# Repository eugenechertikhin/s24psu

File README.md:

This is restore schematic from Studio24 psu for ut88 / rk86

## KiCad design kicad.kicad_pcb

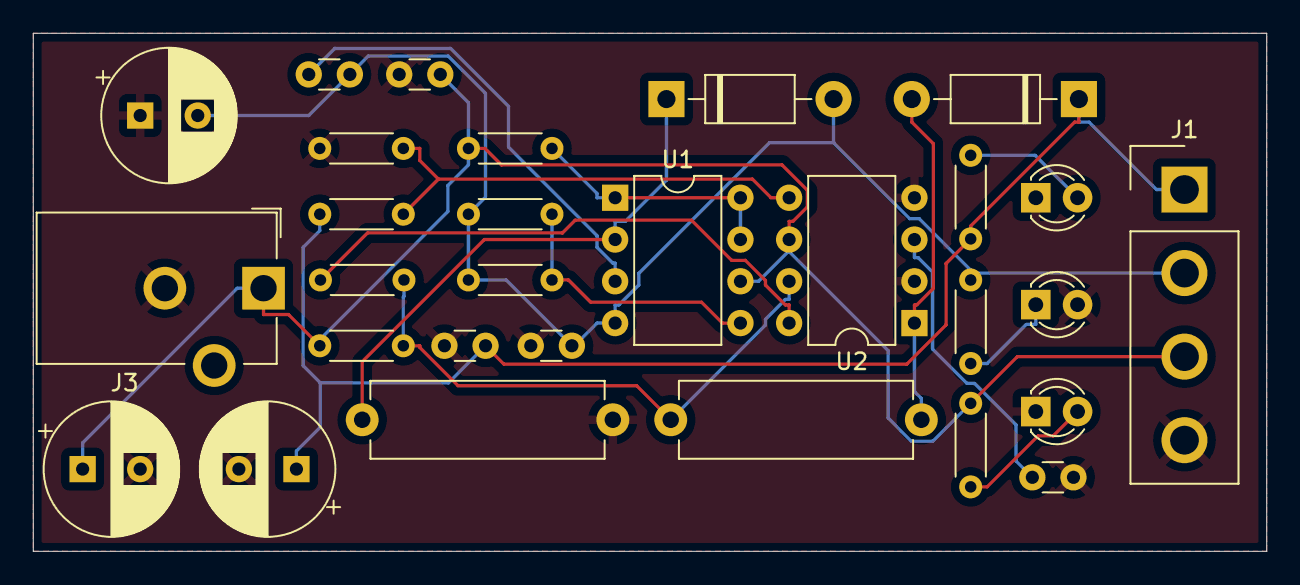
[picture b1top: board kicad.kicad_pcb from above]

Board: 2 copper layers, 75.0 x 31.5 mm, 29 parts (0 on the bottom side), 16 nets.

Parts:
C1, C5, C8: 1000uF 9V; CP_Radial_D8.0mm_P3.50mm
C2, C6: 400pF; C_Disc_D3.0mm_W1.6mm_P2.50mm
C3, C4, C7: 100nF; C_Disc_D3.0mm_W1.6mm_P2.50mm
D1, D4: 1N5819; D_DO-41_SOD81_P10.16mm_Horizontal
D2: yellow; LED_D3.0mm
D3: red; LED_D3.0mm
D5: green; LED_D3.0mm
J1: Power; Samtec_HPM-04-01-x-S_Straight_1x04_Pitch5.08mm
J3: Power IN; BarrelJack_CUI_PJ-102AH_Horizontal
L1, L2: 100uH; L_Axial_L14.0mm_D4.5mm_P15.24mm_Horizontal_Fastron_LACC
R1, R7: 0.33; R_Axial_DIN0204_L3.6mm_D1.6mm_P5.08mm_Horizontal
R2: 3k; R_Axial_DIN0204_L3.6mm_D1.6mm_P5.08mm_Horizontal
R3, R10: 1k; R_Axial_DIN0204_L3.6mm_D1.6mm_P5.08mm_Horizontal
R4, R5: 330; R_Axial_DIN0204_L3.6mm_D1.6mm_P5.08mm_Horizontal
R6: 180; R_Axial_DIN0204_L3.6mm_D1.6mm_P5.08mm_Horizontal
R8: 1.5k; R_Axial_DIN0204_L3.6mm_D1.6mm_P5.08mm_Horizontal
R9: 13k; R_Axial_DIN0204_L3.6mm_D1.6mm_P5.08mm_Horizontal
U1, U2: MC33063AP; DIP-8_W7.62mm

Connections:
+5V: C1.1, C3.1, J1.3, J3.1, R1.2, R5.1, R7.1, U1.6 (Vin), U2.6 (Vin)
+12V: C7.2, C8.1, D4.1 (K), J1.1, R9.2, R10.1
-5V: C2.2, C4.2, C5.2, D1.2 (A), J1.2, R2.1, R3.1, R4.1, U1.4 (GND)
GND: C1.2, C3.2, C4.1, C5.1, C6.2, C7.1, C8.2, D2.2 (A), D3.1 (K), D5.1 (K), J1.4, J3.2, L1.2, R8.1, U2.2 (SwE), U2.4 (GND)
unnamed: D1.1 (K), L1.1, U1.2 (SwE)
unnamed: D2.1 (K), R4.2
unnamed: D3.2 (A), R5.2
unnamed: D4.2 (A), L2.2, U2.1 (SwC)
unnamed: D5.2 (A), R10.2
unnamed: R1.1, U1.1 (SwC), U1.7 (Ipk), U1.8 (DC)
unnamed: C2.1, U1.3 (TC)
unnamed: R2.2, R3.2, U1.5 (Vfb)
unnamed: R6.1, U2.8 (DC)
unnamed: L2.1, R6.2, R7.2, U2.7 (Ipk)
unnamed: C6.1, U2.3 (TC)
unnamed: R8.2, R9.1, U2.5 (Vfb)
